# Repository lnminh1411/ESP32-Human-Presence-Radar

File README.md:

# ESP32 Human Presence Radar

## Companion projects

This board is an add-on to the ESP32 PC Control System, the main project.

| Project | Role for this board |
|---|---|
| [ESP32 PC Control System](https://github.com/lnminh1411/ESP32-PC-Control-System) (main project) | Main desk board. Receives radar and ToF readings over ESP-NOW and runs the presence rules (AFK, away, intruder lock, night) |
| [PC Hardware Control Service](https://github.com/lnminh1411/PC-Hardware-Control-Service) (PcHwCtl) | Windows service. Reads the board over USB and combines it with its webcam presence check |

## About

A small desk presence board: ESP32-S3 SuperMini on a fixed base, HLK LD2410C-P mmWave radar, SR602 PIR and VL53L1X time-of-flight sensor on a sensor head aimed by a two-servo pan-tilt.

The webcam presence check in PcHwCtl fails in the dark (luma 0.1 in low-power mode reads `unknown/dark`) and its depth model can't tell 1.75 m from 2.0 m. Radar and ToF work without light and give a measured distance.

Status: PCB rev 2.2 laid out and routed as two boards joined by a 14-pin FFC: base 32.0 x 42.0 mm (SuperMini, servos, beeper) and sensor head 46.6 x 25.0 mm (radar, PIR, ToF, red indicator LED, LDR), DRC 0/0 on both, Gerbers built, not ordered. No firmware yet, bench tests in `docs/bringup.md`.

## Links

| Link | Peer | Why |
|---|---|---|
| ESP-NOW | ESP32 PC Controller main board | The desk rules (`presence.cpp`, `night.cpp`) run there and must keep working while the PC sleeps or is off |
| USB (24/7, also power) | PcHwCtl service | PcHwCtl combines radar and ToF readings with its camera `presence` check |

## USB identity

Both boards use Espressif's VID, so the PID, product string and WinUSB GUID are how the PC tools tell them apart.

| Field | Radar board | Main board (for comparison) |
|---|---|---|
| VID | `0x303A` | `0x303A` |
| PID | `0x8F52` | `0x1001` |
| Product string | `ESP32 Presence Radar` | `ESP32 PC Controller` |
| Serial | eFuse MAC | eFuse MAC |
| WinUSB interface GUID | `{3195A967-946A-4344-A4CD-F95D1D1FA31E}` | `{39531AD1-55E5-4933-869D-123B4E7D172C}` |

`0x8F52` is not registered with Espressif. On 2026-11-02 their allocated list ended at `0x83E8` and grows upward from there, so this value stays clear for a long time. Register a real PID at github.com/espressif/usb-pids before publishing the hardware.

Details, mounting and open items: [docs/design.md](docs/design.md).

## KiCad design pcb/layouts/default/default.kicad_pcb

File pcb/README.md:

# Presence PCBs (atopile + KiCad), rev 2.2

Two boards joined by a 14-pin 0.5 mm FFC:

- **Base** (32.0 x 42.0 mm, module `Main`, build `default`): fixed on the
  pan-tilt base. ESP32-S3 SuperMini, the two SG90 servo plugs, a second USB-C
  (power only) for the servos, and a PC-case piezo beeper driven through a
  PC817.
- **Sensor head** (46.6 x 25.0 mm, module `Head`, build `head`): rides on
  the two servos. HLK LD2410C-P radar, SR602 PIR and VL53L1X ToF on
  right-angle sockets at the north edge, all facing north, a red
  indicator LED behind the PIR that the firmware drives, and a GL5528 LDR
  under the north edge, facing north with the sensors so the pan-tilt can
  aim it.

Only the light FFC moves with the head, so the servos never pull on a USB
cable. [`main.ato`](main.ato) is the single-file atopile project and the
source of truth for both netlists. Every part is defined locally with
explicit pins; all footprints are stock KiCad except the FFC connector and
the lying C1 (`footprints/PresenceRadar.pretty`, the lying C1 is unused
since rev 2.0). The boards are `layouts/default/default.kicad_pcb` (base) and
`layouts/head/head.kicad_pcb`, built, placed and routed by the scripts in
[`../Scripts/`](../Scripts/Scripts.md).

## Build

```bash
python Scripts/build_board.py base
python Scripts/build_board.py head
```

Each runs `ato build` and the whole chain for one board from a blank board:
netlist sync, layout, pours, routing, chamfers, DRC, renders (add
`--gerbers` for the fab package). `PCB_BOARD=base|head` picks the board
for the single scripts. `ato build` alone needs `PYTHONIOENCODING=utf-8`
(a Windows-console crash in atopile's `designator-map` step); in `ato.yaml`
the version key is `ato-version` (hyphenated).

## Revisions

- 1.0 (2026-11-02): 44 x 45 mm, SuperMini upright with USB-C at the south
  edge, power parts in an east strip. Gerbers built, not ordered.
- 1.1 (2026-11-02): 38.5 x 33.5 mm. SuperMini turned sideways; boost, C2
  and JP1 under it; C1 lying flat; pin labels moved to the bottom.
- 1.2 (2026-11-02): ToF socket moved into the north-west corner (both
  sensors now at the edges), north-west mounting hole moved between the
  sensors, sensor sockets keep their stock silk (a line per pin, pin-1
  hatch) cut at the board edge, pin labels on both sides.
- 1.3 (2026-11-03): 46.6 x 36.5 mm. SR602 PIR added between the two
  sensors, to veto radar motion with no warm body behind it (a fan beside
  the chair). Board now on a rear USB 3.2 Gen 1 port.
- 2.0 (2026-11-03): new outline family, split into a base and a sensor head on a two-servo
  pan-tilt, joined by a 12-pin 0.5 mm FFC. Base adds the servo plugs, a
  6-pin USB-C for the servo 5V (under the SuperMini's own USB-C, both
  cables leaving the west edge) and a piezo beeper. Boost and JP1
  dropped (a boost can go inline in the radar's supply later if the 5V
  pin sags). Pin map redone so the FFC fans straight into the SuperMini
  rows.
- 2.1 (2026-11-03): red indicator LED (D1, 3 mm, two holes) and its 270R
  (R1) on the head right behind the PIR, driven by GPIO5 over FFC base pin
  12 / head pin 1 (was the second GND). Head 46.6 x 25.0 mm (was 21.0) to
  fit it. D1 on the base is now a 1N5819 Schottky (was 1N4007, same DO-41
  holes). Every part's value printed on the top silkscreen.
- 2.2 (2026-11-07): GL5528 LDR on the head (R3, with a 10k R2 and 100 nF
  C3 in 0805) facing north, to measure room light and, aimed by the
  pan-tilt, tell window light from the room lamp. FFC goes to 14 pins: the
  LDR line, and GND back on both ends so a wrong-type cable is harmless
  again. GPIOs remapped so the FFC still fans straight in: LDR GPIO9
  (ADC1), XSHUT GPIO8, INT GPIO7, SDA GPIO6, SCL GPIO5, LED GPIO4, beeper
  GPIO3.

## Board-to-board FFC

Cable: 14-pin, 0.5 mm pitch (a PS4 controller power-switch ribbon), about
0.5 A per conductor. Connectors (J3 on the base, J4 on the head): 14-pin
0.5 mm flip-lock, bottom contact, surface mount. The footprint is drawn
from the store's 20-pin drawing scaled to 14 pins (pads 0.30 x 1.3 mm,
mounting tabs 2.0 x 2.5 mm, body 12.9 mm wide), so check it against the
real part before ordering. The two tabs carry no net; each end GND pad has
a via to the B.Cu pour beside it.

A same-side (type A) cable between the two bottom-contact connectors maps
base pin k to head pin 15 - k. The base cable leaves north, the head cable
leaves south; lay the cable flat between them without a twist or a crease.

| Base pin | Head pin | Net | Base pin | Head pin | Net |
|---|---|---|---|---|---|
| 1 | 14 | `gnd` | 8 | 7 | `tof_xshut` |
| 2 | 13 | `v5` | 9 | 6 | `tof_int` |
| 3 | 12 | `radar_out` | 10 | 5 | `tof_sda` |
| 4 | 11 | `radar_rx` | 11 | 4 | `tof_scl` |
| 5 | 10 | `radar_tx` | 12 | 3 | `led` |
| 6 | 9 | `pir_out` | 13 | 2 | `v3v3` |
| 7 | 8 | `ldr` | 14 | 1 | `gnd` |

The order follows the head west to east (radar, PIR, LDR, ToF, LED last),
so both boards route on F.Cu. GND sits on both ends and the two supplies
on pins 2 and 13: a cable of the other type (k to k) lands GND on GND,
swaps 5V and 3V3 and lands signals on signals, so nothing works but
nothing gets 5V on a signal pin. Before plugging in the sensors, check with
a meter: base J3 pin 2 (or the SuperMini 5V pin) must beep to the head's
radar VCC pin.

## Base board

- 32.0 x 42.0 mm, 1.6 mm, 2 layers. Everything through-hole except the FFC
  connector, the USB-C's six signal pads and the two 0805 CC pull-downs.
  DRC 0/0.
- SuperMini on J1 (north row, side A: 5V GND 3V3 13..8) and J2 (south row,
  side B: TX RX 1..7), rows 15.24 mm apart, **USB-C pointing west**, chip
  and antenna end east. Face up with the USB-C to the right, the 5V row is
  the near row (user-checked 2026-11-02). The last 4.8 mm at the antenna
  end is a copper keepout on both layers.
- North edge: FFC J3, cable leaving north. Its pins 3-8 fan straight down
  into GPIO13..8 (the LDR, pin 7, on GPIO9, an ADC1 pin). Pins 9-12 (ToF
  INT, SDA, SCL, head LED) run east above GPIO8, down the east edge (clear
  of the module's pins, for soldering) and back west under the south row,
  nested, to GPIO7..4. 5V runs under the north row and up between the 3V3
  and GPIO13 pins; 3V3 runs over the connector body to pin 13.
- Under the SuperMini, all under 11 mm (the module's underside):
  - J5, the servo-power USB-C, mouth flush with the west edge right under
    the SuperMini's own USB-C (the receptacle is about 3.2 mm tall, the
    SuperMini's port sits about 12 mm up), so both cables leave the same
    edge and their plugs stack.
  - R4 and R5 (5.1k, 0805) right behind J5's CC pads, to GND.
  - The beeper: 33R (R2), 270R (R1) and the PC817 (U1) standing upright
    (pins 1-2 south, 3-4 north). Stand the resistors upright and press
    them down.
  - J5's two VBUS pads meet over a short B.Cu bridge behind its pads; the
    servo 5V leaves the module area between the TX and RX pins (0.4 mm
    track, the widest that fits between two socket pins).
- South strip: the two servo plugs on a 2x3 header (J4, pan row north, tilt
  row south, signal pins at the east end), the speaker header (J6), the
  1N5819 (D1) and the 10k (R3) lying flat as rungs across J6's pins 1 and 4
  (both 7.62 mm pitch), and C1 on the servo 5V.
- Routing: all F.Cu except J5's VBUS bridge; B.Cu is the GND pour. The
  tight spots are pre-drawn and locked by `layout_base.py` (the four
  east-edge runs, the PIR, LDR and XSHUT fan-out, 5V, J5's CC, GND and
  VBUS stubs),
  because Freerouting boxed tracks in or necked them to 0.15 mm. Net
  classes: Power (`v5`) 0.3 mm, so it fits between 2.54 mm pads and onto
  the FFC's 0.3 mm pads; Servo (`servo_5v`) 0.4 mm; the rest 0.2 mm.
- Mounting holes (M2.5): north-east corner and south-west corner.
- Silkscreen: SuperMini pin labels on both sides, servo rows (TILT, PAN)
  with a `- + S` column legend under the header (top only; added
  2026-11-20 so a servo plug can't go in reversed), speaker + and DRV. Every part's value (270R, 33R, 5.1K, PC817, 1N5819,
  10K, 100uF 25V) is printed on top instead of its reference, inside the
  body outline where there is one (PC817, 1N5819, 10K), next to it
  otherwise; the parts under the module repeat it on the bottom. The
  PC817 outline has no notch: like the PC Controller board, a dot marks
  the pin-1 corner, matching the moulded dot on the part.

## Sensor head

- 46.6 x 25.0 mm, 1.6 mm, 2 layers. DRC 0/0.
- North edge, west to east: radar (J1), PIR (J3), ToF (J2), on right-angle
  sockets whose openings sit 1 mm past the edge. Each module stands at 90
  degrees to the board and faces north. The three modules side by side set
  the board width.
- South edge: FFC J4, cable leaving south toward the base. Every signal
  fans straight up to its socket pin; the radar's 5V reaches the PIR along
  the north side of the radar pins, and the FFC's 5V pin reaches it over
  one short B.Cu hop.
- Silkscreen: sensor pin labels on both sides; each part's value (RED,
  270R, 100uF 25V, 100nF, GL5528) next to it instead of its reference; the
  LDR's 10K and 100nF on the bottom, under the parts (no room on top).
- Right behind the PIR: the red LED D1 (anode west, cathode to the GND
  pour) and its 270R R1 standing west of it. The LED line leaves FFC pin 3
  (east end), runs south under the connector body and comes up to R1.
- North edge, between the PIR and ToF sockets: the GL5528 LDR (R3) is
  fitted from the bottom, its holes one behind the other (the 2.9 mm gap
  between the socket courtyards is too narrow for them side by side). Bend
  both leads 90 degrees so it sits under the board facing north past the
  edge, the south lead 2.5 mm further back. A ~10 mm black tube (heat
  shrink) over it narrows its view to about 30 degrees, so the pan-tilt can
  aim it. 3V3 reaches it from the ToF's VIN along the north side of the ToF
  pins. Below it, on top: R2 10k and C3 100 nF (0805), their GND pads
  facing each other over one via; the LDR line runs straight down to FFC
  pin 8.
- South-west: C1 (100 uF) and C2 (100 nF, pads north-south) on the
  radar's 5V. Mounting holes in both south corners.

## Parts

| Part | Board | Mount | Pin order |
|---|---|---|---|
| ESP32-S3 SuperMini | Base | 2x 1x9 female, vertical, rows 15.24 mm (0.6 in) apart, measured | Side A, USB-C end first: 5V GND 3V3 13 12 11 10 9 8. Side B: TX RX 1 2 3 4 5 6 7 |
| FFC connector x2 | Both | 14-pin 0.5 mm flip-lock, bottom contact, SMD | Pin 1 west on the base, east on the head |
| SG90 servos x2 | Base | J4, 2x3 male; one plug per row | S + - (orange, red, brown); signal pins at the east end, marked `- + S` on the top silkscreen under the header |
| Servo 5V in (J5) | Base | 6-pin power-only USB-C receptacle ("Type-C 6P", 4 through-hole shell legs), stock GCT USB4125 footprint: check the legs against the real part | VBUS x2, GND x2, CC1, CC2; shell legs to GND |
| R4, R5 | Base | 5.1k 0805, behind J5 | CC1, CC2 pull-downs to GND. Without them a USB-C source (C-to-C cable) keeps VBUS off; an A-to-C cable gives 5V either way. Two 10k in parallel (5k) also work |
| PC-case piezo speaker | Base | J6, 1x4 male, motherboard SPEAKER layout | 1 = +5V (east), 4 = drive (west); 2, 3 unused |
| PC817 (U1) | Base | DIP-4 | 1 anode, 2 cathode, 3 emitter, 4 collector |
| R1 270R, R2 33R | Base | standing, 2.54 mm | |
| R3 10k, D1 1N5819 | Base | lying, 7.62 mm | D1 cathode east (to +5V), band = cathode. Schottky 40 V 1 A; a 1N4007 also fits |
| C1 (base) | Base | 100 uF / 25 V, 6.3 x 11 mm, standing | Servo 5V bulk, square pad = + |
| HLK LD2410C-P | Head | 1x5 female, right-angle | TX RX OUT GND VCC (Hi-Link LD2410C manual, table 1) |
| SR602 mini PIR (13.5 mm round board, 10 mm lens) | Head | 1x3 female, right-angle | Front view: - + OUT, so facing north OUT is west; pads GND 5V OUT, east to west. 3.7-12 V (listing; photo says 4.5-20 V); OUT 3.3 V digital, hold 1-18 s |
| VL53L1X breakout (GY-style, silkscreen "VL53L0/1XV2") | Head | 1x6 female, right-angle | VIN GND SCL SDA GPIO1 XSHUT, from the store listing |
| C1 (head) | Head | 100 uF / 25 V, 6.3 x 11 mm, standing. Chosen 2026-11-03: Linh kiện NtShop "Tụ hóa 25V" pack, 100uF/25V x20 | Radar 5V bulk, square pad = + |
| C2 (head) | Head | 100 nF ceramic disc, marked "104", 50 V, 5 mm pitch. Chosen 2026-11-03: "Combo 10 Tụ Gốm 104 100nF 50V" | Radar 5V, high frequency |
| D1 (head) | Head | Red LED, 3 or 5 mm, 2.54 mm leads, standing | Pad 1 (square) = cathode, flat side, short lead |
| R1 (head) | Head | 270R, standing, 2.54 mm | GPIO4 side south; (3.3 - 1.9) / 270 = about 5 mA |
| R3 GL5528 LDR (head) | Head | 5 mm, from the bottom, leads bent 90 degrees to face north | Pad 1 (north) = 3V3, pad 2 = LDR line. About 10-20k at 10 lux, 1M dark, peak 540 nm |
| R2 10k, C3 100 nF (head) | Head | 0805, under the LDR | LDR divider to GND and line filter: ~1.6 V at 10 lux, ~2.6 V at 100 lux |

Apart from the LDR divider the head has no resistors besides the LED's:
the ToF breakout carries its own I2C and XSHUT pull-ups, and the radar's
UART and OUT are 3.3 V push-pull. Check the ToF pin order against the
silkscreen on the real part before soldering.

The FFC connectors, J5's six pads, R4/R5 and the head's R2/C3 are the only
surface-mount parts. The FFC is 0.5 mm pitch: solder it with flux and a fine tip (drag,
then wick bridges), or have the fab place those parts. Solder J5 and R4/R5
before the SuperMini's sockets.

The fit models in the 3D renders are approximate outlines drawn by the
layout scripts, not measured parts.

## Pin map

| GPIO | Net | Use |
|---|---|---|
| 1 | `servo_pan` | Pan servo, 50 Hz LEDC, 500-2400 us |
| 2 | `servo_tilt` | Tilt servo |
| 3 | `beep` | PC817 LED through 270R; a 2-4 kHz square wave = tone |
| 4 | `led` | Head red LED, high = on (about 5 mA) |
| 5 | `tof_scl` | I2C SCL |
| 6 | `tof_sda` | I2C SDA |
| 7 | `tof_int` | ToF GPIO1, data-ready interrupt (open drain) |
| 8 | `tof_xshut` | ToF XSHUT, low = sensor off |
| 9 | `ldr` | LDR, ADC1_CH8; brighter = higher. ADC1 works with Wi-Fi/ESP-NOW on |
| 10 | `pir_out` | PIR OUT, high = warm body moved (3.3 V push-pull) |
| 11 | `radar_tx` | MCU RX from radar TX (UART1, 256000 8N1) |
| 12 | `radar_rx` | MCU TX to radar RX |
| 13 | `radar_out` | Radar OUT, high = presence |

GPIO3 is a strap pin only when an eFuse picks the JTAG source (not set by
default), so the beeper's 270R + opto LED on it is harmless at boot. Kept
free: GPIO43/44 (UART0 boot log), GPIO48 (onboard WS2812 and red LED). No
spare GPIO left on the headers.

The LDR is slow (tens of ms to settle, up to about 1 s from dark), so read
it after the same post-move wait as the radar and PIR. Paired with the
ToF's ambient rate (940 nm IR, which LED lamps barely emit), it tells
daylight from lamp light: LDR high + ambient high = daylight, LDR high +
ambient near zero = lamp.

## Power

Two USB cables, both on rear panel ports, grounds shared:

- SuperMini USB-C, on a rear USB 2.0 port (500 mA; the SuperMini is a USB
  2.0 full-speed device). Its 5V and 3V3 pins are outputs: 5V feeds the
  radar and the PIR, 3V3 the ToF, both over the FFC. Estimated draw about
  200 mA average and about 470 mA peak (ESP32 transmit bursts about
  340 mA, radar about 100 mA, the rest about 25 mA), from datasheets, not
  measured yet. Lowering the Wi-Fi transmit power (the main board runs
  8 dBm) cuts the ESP32's peak to about 200 mA.
- Servo USB-C (J5, second USB, power only), on a rear USB 3.2 Gen 1 port
  (900 mA): net `servo_5v` feeds both servos and the beeper, with C1 on
  the base. It never touches `v5`, so neither port can push current into
  the other, and servo and beep current stays off the sensors' supply. An
  SG90 draws up to about 650 mA stalled, so moving both at once can pass
  the port's 900 mA: move one servo at a time, ramp each move, stop the
  pulses when it ends, and never drive into the end stops.

Use ports on different fuse groups where possible: motherboard ports often
share one polyfuse per pair, which would see both cables together.

These two ports replace the rev 1.3-2.2 plan of the SuperMini on the USB
3.2 Gen 1 port (decided 2026-11-15).

No diode on 5V: with one source per rail there is nothing to backfeed. A
Schottky in series would put the radar under Hi-Link's 5 V minimum.

The head's C1 sits on the SuperMini's VBUS, over the USB limit of 10 uF at
attach, so plugging in draws a short inrush spike. Rear panel ports are
current-limited and handle it. If the port ever browns out on plug-in,
lower C1 to 47 uF or add a soft-start; a diode does not fix inrush.

## Beeper

GPIO3 -> R1 270R -> PC817 LED (about 8 mA); the PC817's transistor pulls
the speaker's drive pin to GND through R2 33R, with the speaker's other pin
on `servo_5v`. The PC817's 50 mA output limit sets the beep current. R3 10k
across the speaker lets the piezo discharge between pulses; D1 clamps the
kick if a magnetic buzzer is ever plugged in instead.

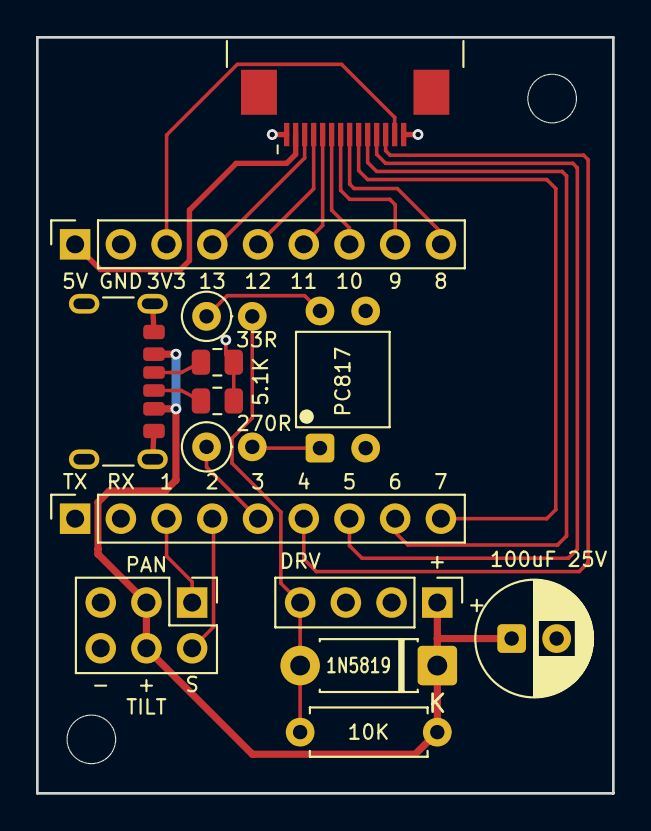
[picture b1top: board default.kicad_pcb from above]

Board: 2 copper layers, 32.0 x 42.0 mm, 17 parts (0 on the bottom side), 22 nets.

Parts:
C1: 100u 25V; CP_Radial_D6.3mm_P2.50mm
D1: 1N5819; D_DO-41_SOD81_P7.62mm_Horizontal
FIT1: (no value)
J1, J2: main.ato:Socket1x9; PinSocket_1x09_P2.54mm_Vertical
J3: main.ato:Ffc14; FFC_P0.50mm_1x14_FlipLock_Bottom
J4: main.ato:ServoHeader2x3; PinHeader_2x03_P2.54mm_Vertical
J5: main.ato:UsbC6P; USB_C_Receptacle_GCT_USB4125-xx-x_6P_TopMnt_Horizontal
J6: main.ato:SpeakerHeader; PinHeader_1x04_P2.54mm_Vertical
MH1, MH2: MountingHole_2.7mm_M2.5
R1: 270; R_Axial_DIN0207_L6.3mm_D2.5mm_P2.54mm_Vertical
R2: 33; R_Axial_DIN0207_L6.3mm_D2.5mm_P2.54mm_Vertical
R3: 10k; R_Axial_DIN0207_L6.3mm_D2.5mm_P7.62mm_Horizontal
R4, R5: 5.1k; R_0805_2012Metric
U1: PC817; DIP-4_W7.62mm

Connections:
beep: J2.5, R1.1
beep_led: R1.2, U1.1
cc1: J5.A5, R4.1
cc2: J5.B5, R5.1
gnd: C1.2, J1.2, J3.1, J3.14, J4.5, J4.6, J5.A12, J5.B12, J5.SH, R4.2, R5.2, U1.2, U1.3
ldr: J1.8, J3.7
led: J2.6, J3.12
opto_c: R2.1, U1.4
pir_out: J1.7, J3.6
radar_out: J1.4, J3.3
radar_rx: J1.5, J3.4
radar_tx: J1.6, J3.5
servo_5v: C1.1, D1.1, J4.3, J4.4, J5.A9, J5.B9, J6.1, R3.1
servo_pan: J2.3, J4.1
servo_tilt: J2.4, J4.2
spk_drive: D1.2, J6.4, R2.2, R3.2
tof_int: J2.9, J3.9
tof_scl: J2.7, J3.11
tof_sda: J2.8, J3.10
tof_xshut: J1.9, J3.8
v3v3: J1.3, J3.13
v5: J1.1, J3.2

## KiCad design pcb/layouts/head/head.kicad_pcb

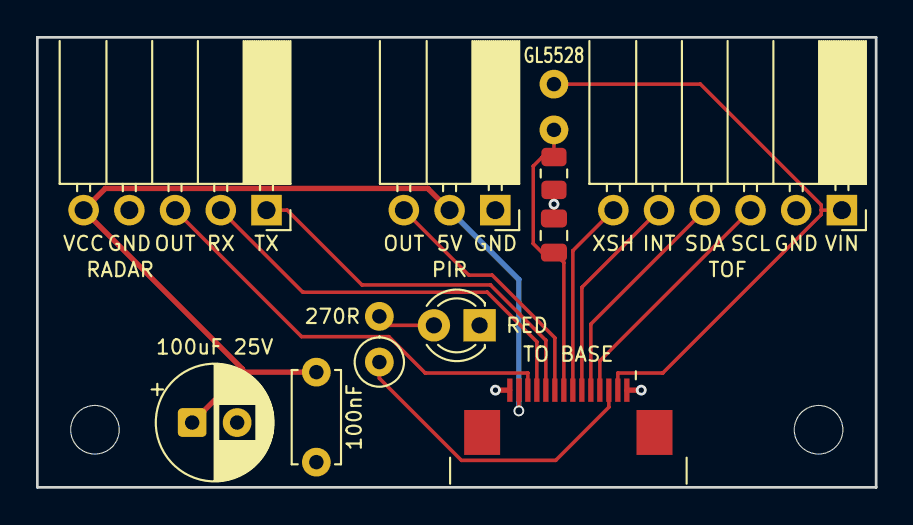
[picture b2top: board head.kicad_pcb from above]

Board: 2 copper layers, 46.6 x 25.0 mm, 14 parts (1 on the bottom side), 14 nets.

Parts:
C1: 100u 25V; CP_Radial_D6.3mm_P2.50mm
C2: 100n; C_Disc_D5.0mm_W2.5mm_P5.00mm
C3: 100n; C_0805_2012Metric
D1: RED; LED_D3.0mm
FIT1: (no value)
J1: main.ato:RadarSocket; PinSocket_1x05_P2.54mm_Horizontal
J2: main.ato:TofSocket; PinSocket_1x06_P2.54mm_Horizontal
J3: main.ato:PirSocket; PinSocket_1x03_P2.54mm_Horizontal
J4: main.ato:Ffc14; FFC_P0.50mm_1x14_FlipLock_Bottom
MH1, MH2: MountingHole_2.7mm_M2.5
R1: 270; R_Axial_DIN0207_L6.3mm_D2.5mm_P2.54mm_Vertical
R2: 10k; R_0805_2012Metric
R3: GL5528; R_LDR_4.9x4.2mm_P2.54mm_Vertical

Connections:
gnd: C1.2, C2.2, C3.2, D1.1, J1.4, J2.2, J3.1, J4.1, J4.14, R2.2
ldr: C3.1, J4.8, R2.1, R3.2
led: J4.3, R1.1
led_a: D1.2, R1.2
pir_out: J3.3, J4.9
radar_out: J1.3, J4.12
radar_rx: J1.2, J4.11
radar_tx: J1.1, J4.10
tof_int: J2.5, J4.6
tof_scl: J2.3, J4.4
tof_sda: J2.4, J4.5
tof_xshut: J2.6, J4.7
v3v3: J2.1, J4.2, R3.1
v5: C1.1, C2.1, J1.5, J3.2, J4.13
